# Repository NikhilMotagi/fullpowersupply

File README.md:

# fullpowersupply
This is my first try at designing a PCB with just fill zones 

This technique covers most of the copper and hence no issue related trace widhts.

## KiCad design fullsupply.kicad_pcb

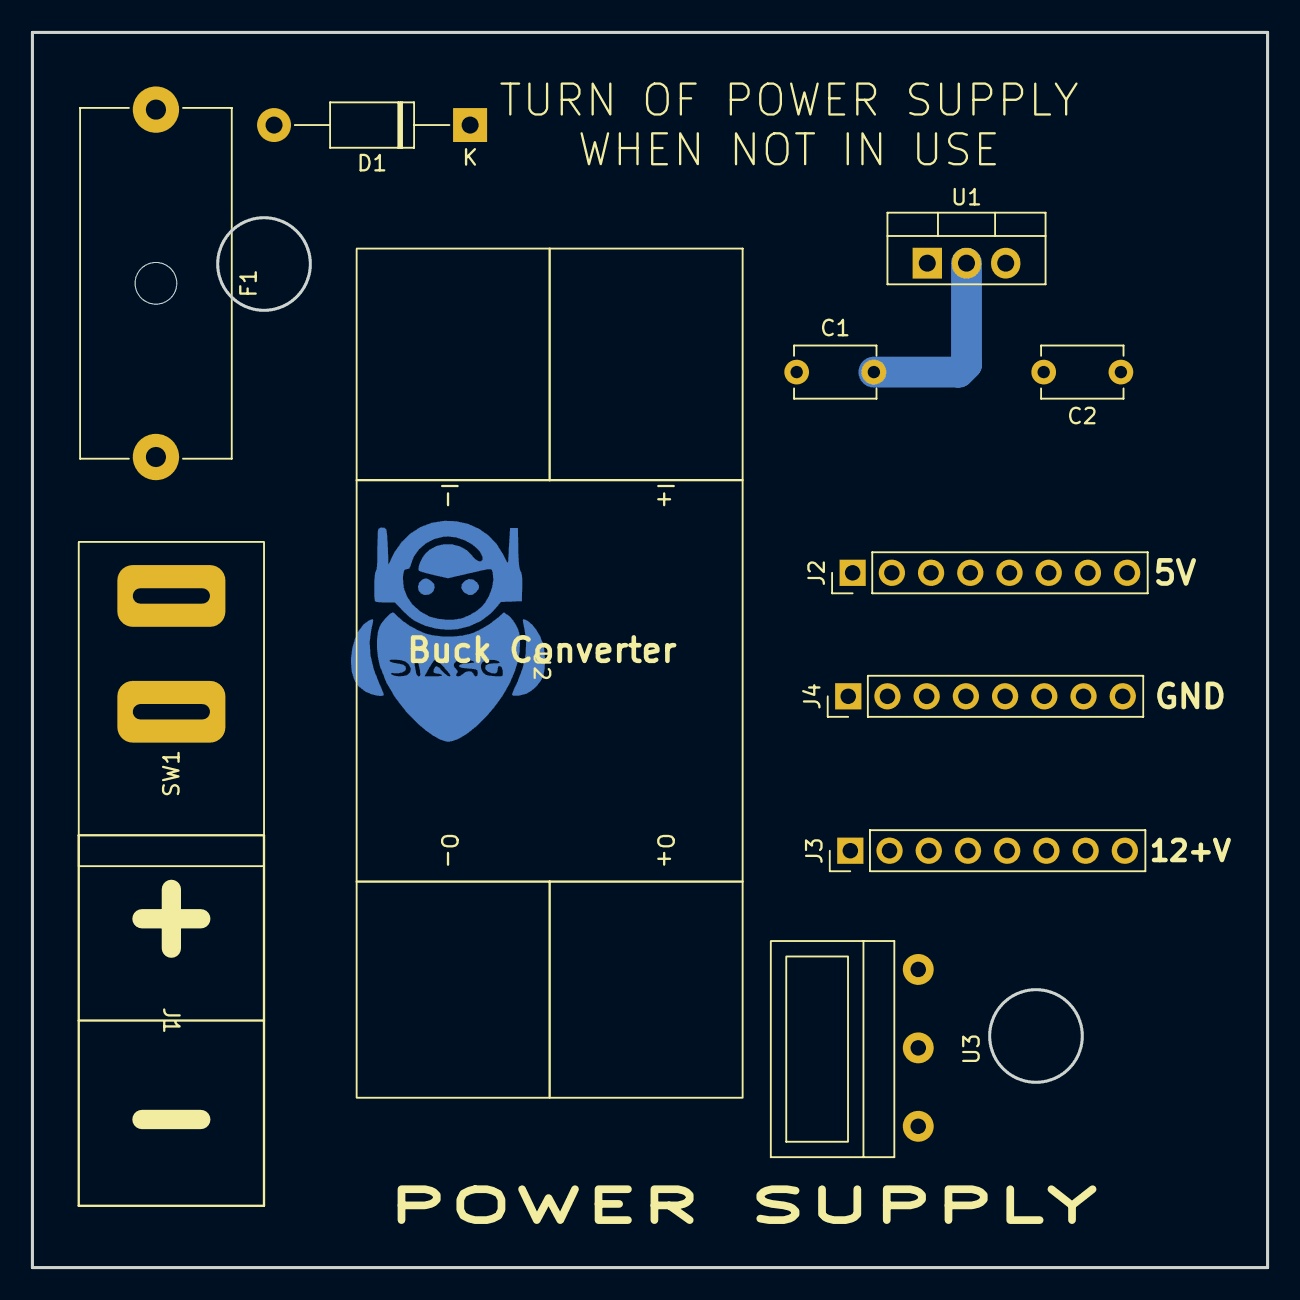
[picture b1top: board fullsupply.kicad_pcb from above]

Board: 2 copper layers, 80.0 x 80.0 mm, 13 parts (0 on the bottom side), 7 nets.

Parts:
Buck Converter: LOGO; draic logo
C1, C2: 100u; C_Disc_D5.1mm_W3.2mm_P5.00mm
D1: 1N4007; D_DO-41_SOD81_P12.70mm_Horizontal
F1: Fuse; Fuseholder_Cylinder-5x20mm_Schurter_0031_8201_Horizontal_Op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
J1: INPUT; PowerEdge
J2: 5V; PinHeader_1x08_P2.54mm_Vertical
J3: VCC12+; PinHeader_1x08_P2.54mm_Vertical
J4: GND; PinHeader_1x08_P2.54mm_Vertical
SW1: SW_DIP_x01; DPDT_SW
U1: LM7805_TO220; TO-220-3_Vertical
U2: BUCK CONVERTER; Buckconverter
U3: Digitalvoltmeter; DigitalVoltmeter

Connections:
5V: C2.1, J2.1, J2.2, J2.3, J2.4, J2.5, J2.6, J2.7, J2.8, U1.3 (VO), U3.1 (VCC)
GND: C1.2, C2.2, J1.2, J4.1, J4.2, J4.3, J4.4, J4.5, J4.6, J4.7, J4.8, U1.2 (GND), U2.2, U2.4, U3.2 (GND)
MVCC: C1.1, D1.1 (K), U1.1 (VI), U2.1
unnamed: D1.2 (A), F1.1
unnamed: F1.2, SW1.2
unnamed: J1.1, SW1.1
VCC12+: J3.1, J3.2, J3.3, J3.4, J3.5, J3.6, J3.7, J3.8, U2.3, U3.3 (VIN)

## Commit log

2022-09-24 fill pcb
